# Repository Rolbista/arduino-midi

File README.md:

# MidiBoi™

MidiBoi™ is a controller designed for use with Korg® Monologue™. It is literally just two reprogrammable mod wheels.  
Because Monologue™ only has one pitch-stick, dynamic modulation is limited when playing by hand since it's  impossible  
to do, for example, pitch bend and add vibrato at the same time conveniently. LFO int knob is on the other side of  
the synthesizer. Why not use a standard MIDI keyboard with normal wheels then? Well, while standard Pitch Bend MIDI  
message is accepted and interpreted by the synth, Mod Wheel message is not. LFO intensity is assigned to MIDI CC 26  
so it won't react unless you reprogram the wheel to send it. I could not find a controller that would let me do this,  
space was also a consideration - since the Monologue™ already has a keyboard and doesn't exist in a module form apart  
from some risky looking mods, why take up space with another if two wheels are all that is necessary to add  
expressiveness to the interface? Potentiometers with programmable CC messages are useful in cases where hardware is  
fixed and cannot easily accept a different value like you would on a DAW by just using MIDI Learn. While it was built  
with a specific model in mind, this can be used with other synthesizers as well if you need additional mod wheel or  
two or want a comfortable wheel to steer a parameter not present on the panel.

## Setup  

The default selected board is Arduino Pro Micro or clone because of its small size and native USB capability which  
allows you to use it with your DAW without any extra fuss. The library dependencies are in the sketch.  
Open the `./switcher_one_pot.ino` sketch, update the pins as appropriate and upload it.

## Usage

MidiBoi™ is powered by USB, just plug one of those old phone chargers that you have lying around that will surely  
come in handy one day - now is their time to shine! Use a standard DIN MIDI cable to connect MidiBoi™ output to  
synth MIDI input. Default CC are 26 (LFO intensity) for wheel 1 and 24 (LFO rate) for wheel 2. When the controller  
powers up it works in default, loop mode, sending default messages. To reprogram wheel 1 push the encoder button once,  
select the desired wheel number (1), press the button again. Now select new CC message (0-119) keeping in mind your  
synths MIDI implementation. Press the button again to save the change. Now wheel one send a new CC message and you  
instrument should react accordingly.  
  
To save potentiometer settings to persistent memory double press the encoder while in `PLAY`/`LOOP` mode.  
A `SAVE` message should display for 1,5 seconds and return to normal.  

## Features

* Segment display showing current wheel/potentiometer/MIDI CC selected
* Encoder for value input
* Support for n potentiometers with reprogrammable CCs limited only by number of ADC pins on selected Arduino board
* Support for storing and saving potentiometer configs in EEPROM  
* USB and DIN5 MIDI output on channel 1
* Extensibility: with little modification of the hardware any MIDI parameter can be controlled with any type of analog device - add a jack for an expression pedal if you like

## Roadmap  

* Software MIDI passthrough so the only DIN jack on target synth is not taken up
* Possibly OLED screen for clearer information display
* Channel reprogrammability
* Higher bit resolution (10 bit, allowed by Control-Surface library)
* Example PCB design (Kicad single-sided board)

## Additional info

Libraries used:  
https://github.com/tttapa/Control-Surface  
https://github.com/mathertel/RotaryEncoder  
https://github.com/avishorp/TM1637  
https://github.com/mathertel/OneButton  

Monologue MIDI Implementation Chart:  
https://www.korg.com/us/support/download/manual/0/733/3519/  
https://bit.ly/2ZH0zTO (page 58)

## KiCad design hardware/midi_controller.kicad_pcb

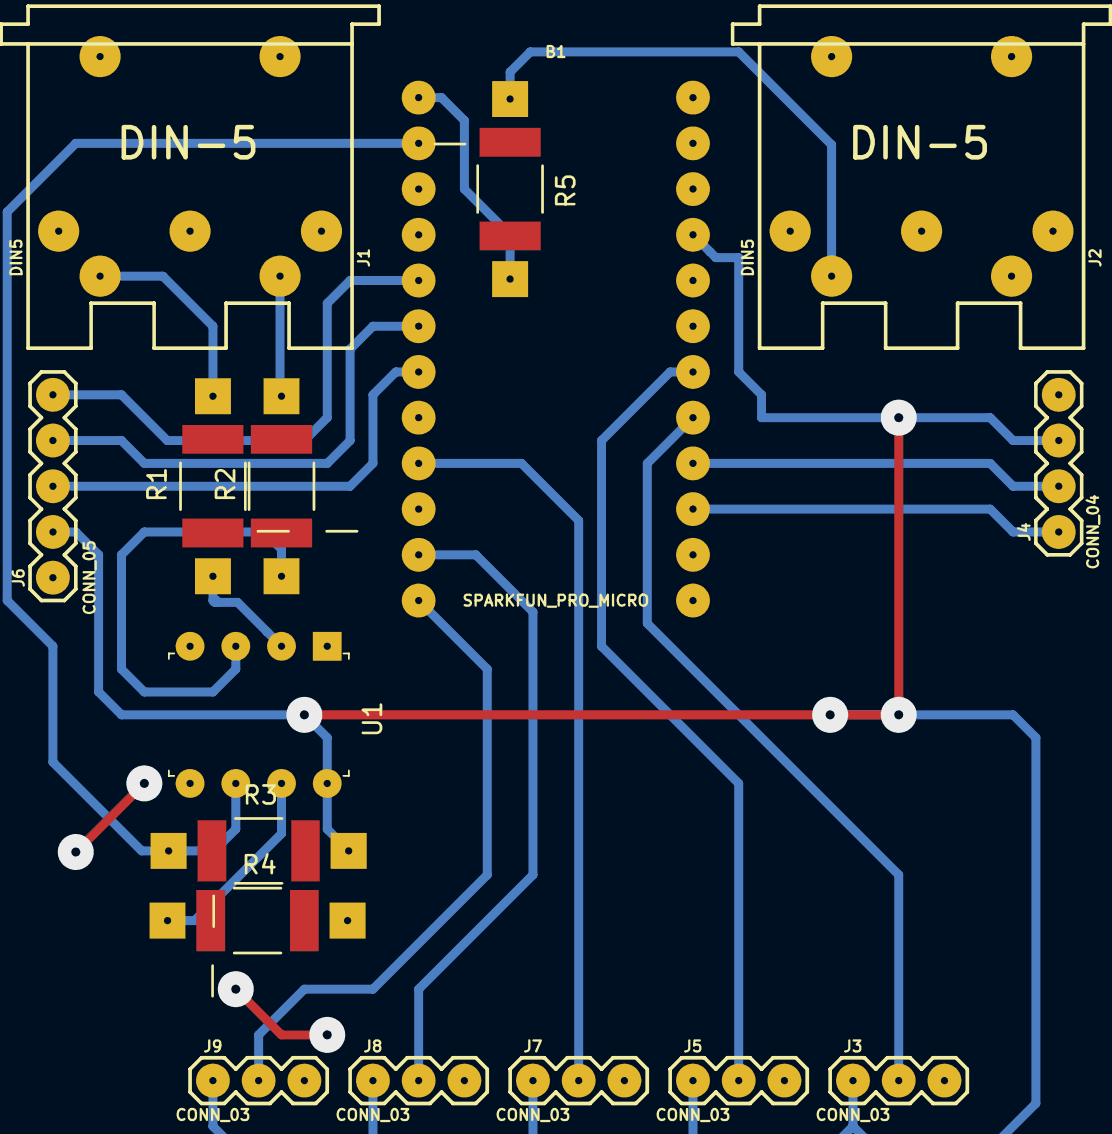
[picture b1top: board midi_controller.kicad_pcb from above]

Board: 2 copper layers, 16 parts (0 on the bottom side), 20 nets.

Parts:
B1: SPARKFUN_PRO_MICRO
J1, J2: DIN5; DIN5-RA-PTH
J3, J5, J7, J8, J9: CONN_03; 1X03
J4: CONN_04; 1X04
J6: CONN_05; 1X05
R1, R2, R3, R4, R5: RESISTOR0402; Resistor_SMD+THTuniversal_2512_RM10_HandSoldering_RevA_Date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
U1: 6N137; DIP-8_W7.62mm

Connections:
GND: B1.23, J2.5, J3.3, J4.4, J5.3, J6.1, J7.3, J8.3, J9.3, R4.2, U1.5
unnamed: B1.1, R5.2
unnamed: B1.2, R3.1, U1.6
unnamed: B1.5, J6.5
unnamed: B1.6, J6.4
unnamed: B1.7, J6.3
unnamed: B1.9, J7.2
unnamed: B1.11, J8.2
unnamed: B1.12, J9.2
unnamed: B1.15, J4.1
unnamed: B1.16, J4.2
unnamed: B1.17, J3.2
unnamed: B1.18, J5.2
unnamed: B1.21, J3.1, J4.3, J5.1, J6.2, J7.1, J8.1, J9.1, R3.2, U1.8
unnamed: J1.4, R1.2
unnamed: J1.5, R2.2
unnamed: J2.4, R5.1
unnamed: R1.1, U1.2
unnamed: R2.1, U1.3
unnamed: R4.1, U1.7

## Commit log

2017-06-29 added .gitignore
2017-10-19 initial wobbly analogread
2019-05-08 elo pawel
2019-05-25 working DIN5 midi output
2020-01-02 move encoder value display to encoderConfig() function for performance, use Button class for encoder button, refactor switch cases for readability
    add variable range to encoder
    encoder stays at saved value but is too slow to be usable
    works a bit better but still too slow, pot select doesn't work or is too slow to notice
    add encoder pointer parameter to function
    change CC message number variable to array to index with potentiometer number
    set config mode encoder start position to recent for n potentiometers
2020-01-02 add circuit schematic, pcb design files and front panel layout
2020-01-02 fix analog pins and remove redundant resistor
2020-01-14 introduce a new button library to enable double click, move mode check to a function to enable button callbacks
